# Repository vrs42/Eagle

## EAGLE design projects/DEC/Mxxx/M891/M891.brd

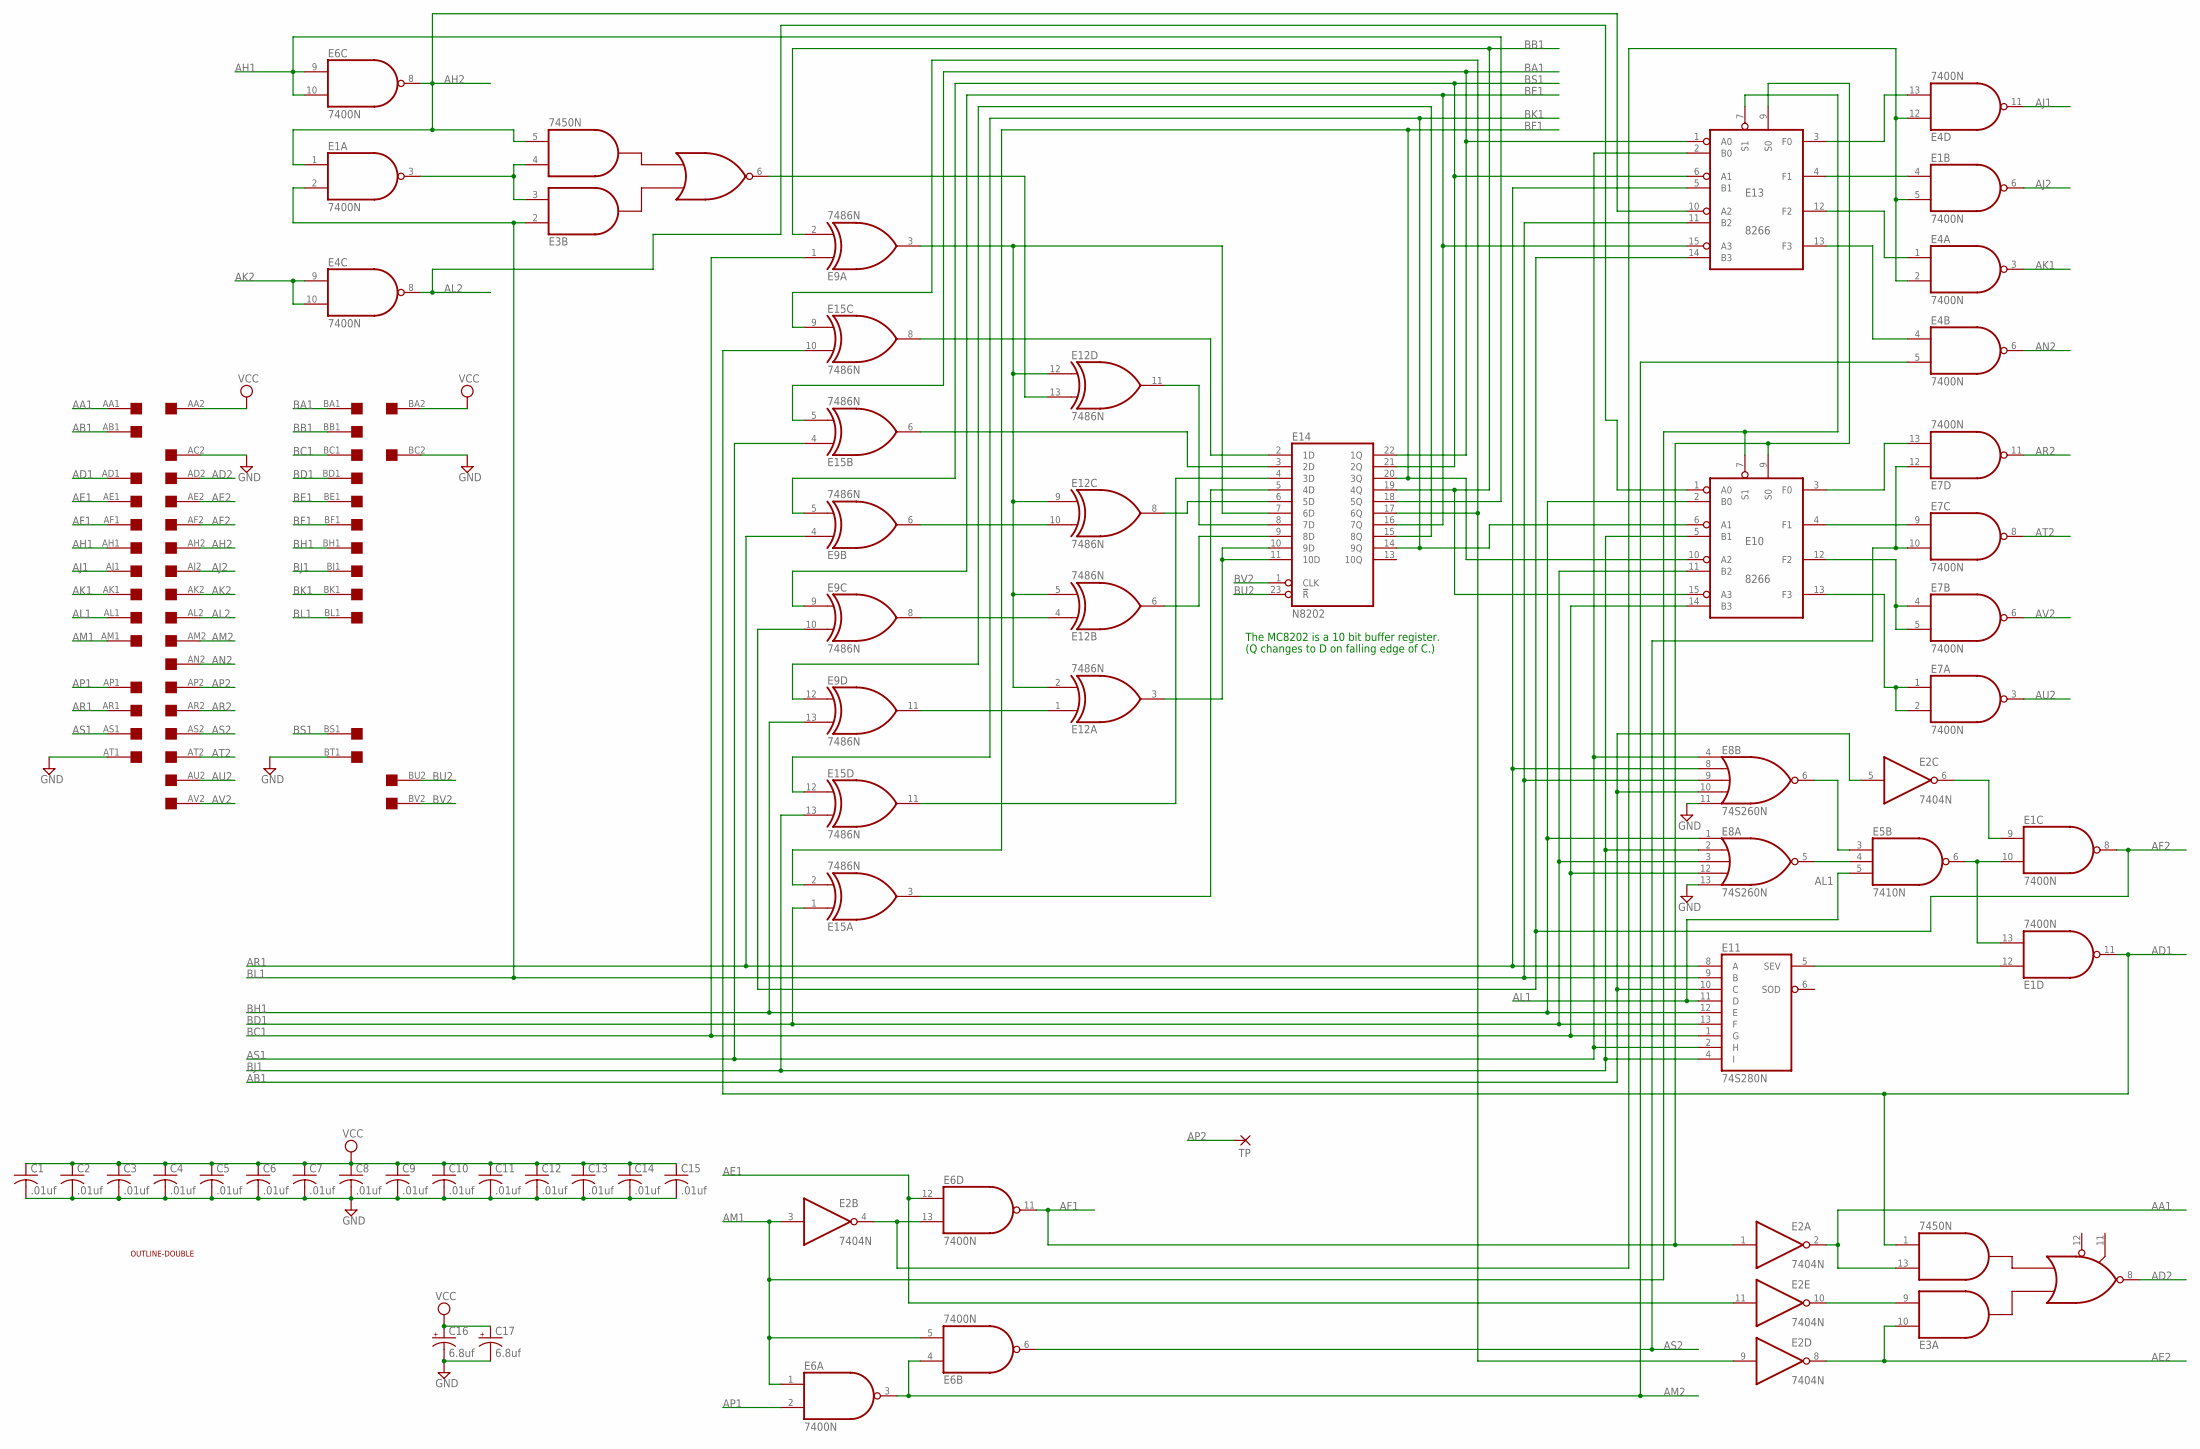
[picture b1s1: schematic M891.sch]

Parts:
C1, C2, C3, C4, C5, C6, C7, C8, C9, C10, C11, C12, C13, C14, C15: .01uf; C050-025X075
C16, C17: 6.8uf; E22-6
E1, E4, E6, E7: 7400N; DIL14
E2: 7404N; DIL14
E3: 7450N; DIL14
E5: 7410N; DIL14
E8: 74S260N; DIL14
E9, E12, E15: 7486N; DIL14
E10, E13: 8266; DIL16
E11: 74S280N; DIL14
E14: N8202; DIL24
EDGE: DOUBLE; EDGE-CON4
TP: 2,15/1,0
U$2: OUTLINE-DOUBLE; DOUBLE

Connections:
AA1: E2.2 (O), E3.13 (I3), EDGE.AA1
AB1: E2.5 (I), E8.10 (I3), E11.10 (C), EDGE.AB1
AD1: E1.11 (O), E3.1 (I4), E15.10 (I1), EDGE.AD1
AD2: E3.8 (O), EDGE.AD2
AE1: E2.11 (I), E6.12 (I0), EDGE.AE1
AE2: E2.8 (O), E3.10 (I1), EDGE.AE2
AF1: E2.1 (I), E6.11 (O), E10.9 (S0), E13.9 (S0), EDGE.AF1
AF2: E1.8 (O), E9.10 (I1), E13.14 (B3), EDGE.AF2
AH1: E6.9 (I0), E6.10 (I1), E14.18 (5Q), EDGE.AH1
AH2: E1.1 (I0), E3.5 (I4), E6.8 (O), E13.10 (A2), EDGE.AH2
AJ1: E4.11 (O), EDGE.AJ1
AJ2: E1.6 (O), EDGE.AJ2
AK1: E4.3 (O), EDGE.AK1
AK2: E4.9 (I0), E4.10 (I1), EDGE.AK2
AL1: E5.5 (I2), E11.11 (D), EDGE.AL1
AL2: E4.8 (O), E10.1 (A0), EDGE.AL2
AM1: E2.3 (I), E6.1 (I0), E6.5 (I1), E10.7 (S1), E13.7 (S1), EDGE.AM1
AM2: E4.5 (I1), E6.3 (O), E6.4 (I0), EDGE.AM2
AN2: E4.6 (O), EDGE.AN2
AP1: E6.2 (I1), EDGE.AP1
AP2: EDGE.AP2, TP.1
AR1: E8.8 (I1), E9.4 (I0), E11.8 (A), E13.5 (B1), EDGE.AR1
AR2: E7.11 (O), EDGE.AR2
AS1: E8.4 (I0), E11.2 (H), E13.2 (B0), E15.4 (I0), EDGE.AS1
AS2: E6.6 (O), E7.10 (I1), E7.12 (I0), EDGE.AS2
AT2: E7.8 (O), EDGE.AT2
AU2: E7.3 (O), EDGE.AU2
AV2: E7.6 (O), EDGE.AV2
BA1: E13.1 (A0), E14.22 (1Q), E15.5 (I1), EDGE.BA1
BB1: E9.2 (I1), E10.15 (A3), E14.19 (4Q), EDGE.BB1
BC1: E8.12 (I3), E9.1 (I0), E10.14 (B3), E11.1 (G), EDGE.BC1
BD1: E8.3 (I2), E10.11 (B2), E11.13 (F), E15.1 (I0), EDGE.BD1
BE1: E9.9 (I0), E13.15 (A3), E14.16 (7Q), EDGE.BE1
BF1: E10.10 (A2), E14.20 (3Q), E15.2 (I1), EDGE.BF1
BH1: E8.1 (I0), E9.13 (I1), E10.2 (B0), E11.12 (E), EDGE.BH1
BJ1: E8.2 (I1), E10.5 (B1), E11.4 (I), E15.13 (I1), EDGE.BJ1
BK1: E10.6 (A1), E14.14 (9Q), E15.12 (I0), EDGE.BK1
BL1: E1.2 (I1), E3.2 (I1), E8.9 (I2), E11.9 (B), E13.11 (B2), EDGE.BL1
BS1: E9.5 (I1), E13.6 (A1), E14.21 (2Q), EDGE.BS1
BU2: E14.23 (!R), EDGE.BU2
BV2: E14.1 (CLK), EDGE.BV2
GND: C1.2, C2.2, C3.2, C4.2, C5.2, C6.2, C7.2, C8.2, C9.2, C10.2, C11.2, C12.2, C13.2, C14.2, C15.2, C16.-, C17.-, E1.7 (GND), E2.7 (GND), E3.7 (GND), E4.7 (GND), E5.7 (GND), E6.7 (GND), E7.7 (GND), E8.7 (GND), E8.11 (I4), E8.13 (I4), E9.7 (GND), E10.8 (GND), E11.7 (GND), E12.7 (GND), E13.8 (GND), E14.12 (GND), E15.7 (GND), EDGE.AC2, EDGE.AT1, EDGE.BC2, EDGE.BT1
unnamed: E1.3 (O), E3.3 (I2), E3.4 (I3)
unnamed: E2.9 (I), E14.17 (6Q), E15.9 (I0)
unnamed: E1.5 (I1), E2.4 (O), E4.2 (I1), E4.12 (I0), E6.13 (I1)
unnamed: E4.13 (I1), E13.3 (F0)
unnamed: E1.4 (I0), E13.4 (F1)
unnamed: E4.1 (I0), E13.12 (F2)
unnamed: E4.4 (I0), E13.13 (F3)
unnamed: E9.12 (I0), E14.15 (8Q)
unnamed: E3.6 (O), E12.13 (I1)
unnamed: E1.12 (I0), E11.5 (SEV)
unnamed: E14.3 (2D), E15.6 (O)
unnamed: E9.3 (O), E12.2 (I1), E12.5 (I1), E12.9 (I0), E12.12 (I0), E14.7 (6D)
unnamed: E9.11 (O), E12.1 (I0)
unnamed: E9.8 (O), E12.4 (I0)
unnamed: E9.6 (O), E12.10 (I1)
unnamed: E14.2 (1D), E15.8 (O)
unnamed: E12.11 (O), E14.8 (7D)
unnamed: E14.5 (4D), E15.3 (O)
unnamed: E14.4 (3D), E15.11 (O)
unnamed: E12.8 (O), E14.6 (5D)
unnamed: E12.6 (O), E14.9 (8D)
unnamed: E12.3 (O), E14.10 (9D), E14.11 (10D)
unnamed: E7.9 (I0), E10.4 (F1)
unnamed: E7.13 (I1), E10.3 (F0)
unnamed: E7.4 (I0), E7.5 (I1), E10.12 (F2)
unnamed: E7.1 (I0), E7.2 (I1), E10.13 (F3)
unnamed: E2.10 (O), E3.9 (I2)
unnamed: E5.4 (I1), E8.5 (O)
unnamed: E5.3 (I0), E8.6 (O)
unnamed: E1.10 (I1), E1.13 (I1), E5.6 (O)
unnamed: E1.9 (I0), E2.6 (O)
VCC: C1.1, C2.1, C3.1, C4.1, C5.1, C6.1, C7.1, C8.1, C9.1, C10.1, C11.1, C12.1, C13.1, C14.1, C15.1, C16.+, C17.+, E1.14 (VCC), E2.14 (VCC), E3.14 (VCC), E4.14 (VCC), E5.14 (VCC), E6.14 (VCC), E7.14 (VCC), E8.14 (VCC), E9.14 (VCC), E10.16 (VCC), E11.14 (VCC), E12.14 (VCC), E13.16 (VCC), E14.24 (VCC), E15.14 (VCC), EDGE.AA2, EDGE.BA2

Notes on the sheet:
The MC8202 is a 10 bit buffer register.
(Q changes to D on falling edge of C.)

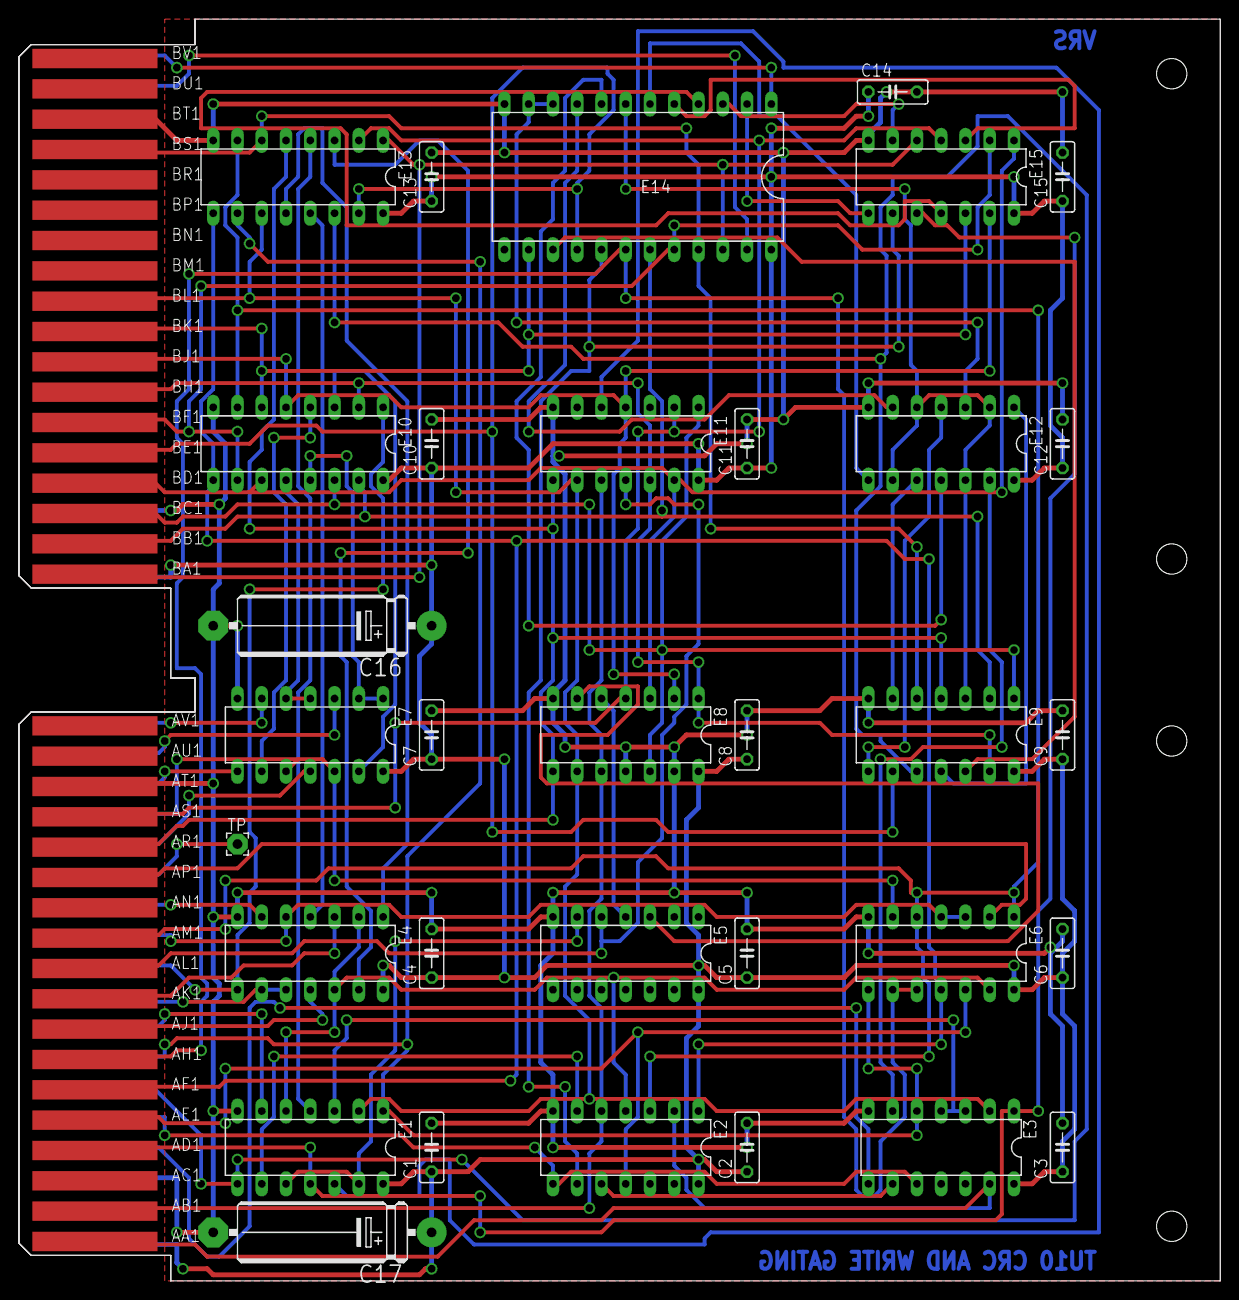
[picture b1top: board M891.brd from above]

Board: 2 copper layers, 125.7 x 132.1 mm, 35 parts (0 on the bottom side), 74 nets.

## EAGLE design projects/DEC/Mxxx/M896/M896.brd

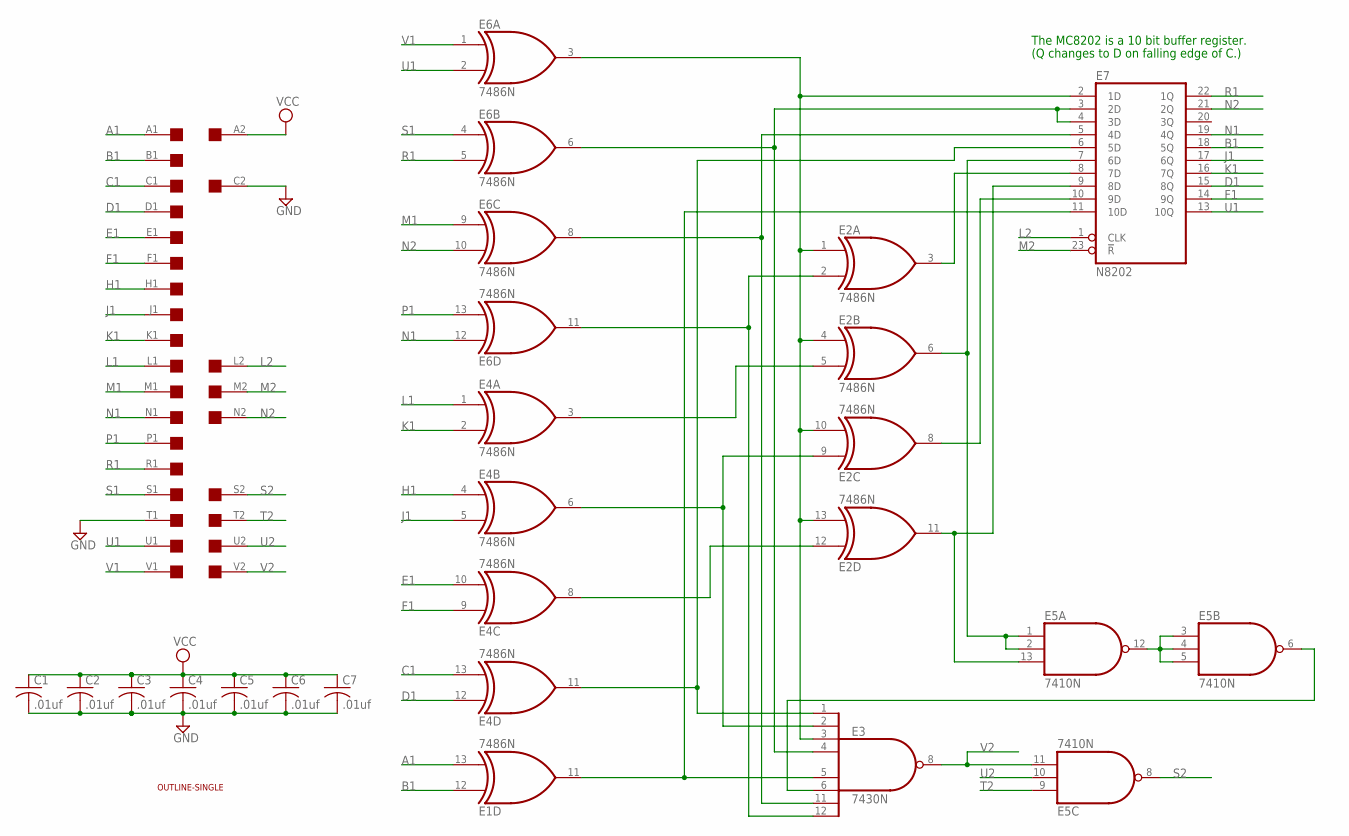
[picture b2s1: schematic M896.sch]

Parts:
C1, C2, C3, C4, C5, C6, C7: .01uf; C050-025X075
E1, E2, E4, E6: 7486N; DIL14
E3: 7430N; DIL14
E5: 7410N; DIL14
E7: N8202; DIL24
U$1: EDGE-2CONNECTOR; EDGE-CON2
U$4: OUTLINE-SINGLE; SINGLE

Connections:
A1: E1.13 (I1), U$1.A1
B1: E1.12 (I0), E7.18 (5Q), U$1.B1
C1: E4.13 (I1), U$1.C1
D1: E4.12 (I0), E7.15 (8Q), U$1.D1
E1: E4.10 (I1), U$1.E1
F1: E4.9 (I0), E7.14 (9Q), U$1.F1
GND: C1.2, C2.2, C3.2, C4.2, C5.2, C6.2, C7.2, E1.7 (GND), E2.7 (GND), E3.7 (GND), E4.7 (GND), E5.7 (GND), E6.7 (GND), E7.12 (GND), U$1.C2, U$1.T1
H1: E4.4 (I0), U$1.H1
J1: E4.5 (I1), E7.17 (6Q), U$1.J1
K1: E4.2 (I1), E7.16 (7Q), U$1.K1
L1: E4.1 (I0), U$1.L1
L2: E7.1 (CLK), U$1.L2
M1: E6.9 (I0), U$1.M1
M2: E7.23 (!R), U$1.M2
N1: E6.12 (I0), E7.19 (4Q), U$1.N1
N2: E6.10 (I1), E7.21 (2Q), U$1.N2
unnamed: E2.1 (I0), E2.4 (I0), E2.10 (I1), E2.13 (I1), E3.3 (I2), E6.3 (O), E7.2 (1D)
unnamed: E2.2 (I1), E3.12 (I7), E6.11 (O)
unnamed: E2.5 (I1), E4.3 (O)
unnamed: E2.9 (I0), E3.2 (I1), E4.6 (O)
unnamed: E2.12 (I0), E4.8 (O)
unnamed: E1.11 (O), E3.5 (I4), E7.11 (10D)
unnamed: E3.1 (I0), E4.11 (O), E7.6 (5D)
unnamed: E5.3 (I0), E5.4 (I1), E5.5 (I2), E5.12 (O)
unnamed: E3.11 (I6), E6.8 (O), E7.5 (4D)
unnamed: E3.4 (I3), E6.6 (O), E7.3 (2D), E7.4 (3D)
unnamed: E3.6 (I5), E5.6 (O)
unnamed: E2.6 (O), E5.1 (I0), E5.2 (I1), E7.7 (6D)
unnamed: E2.11 (O), E5.13 (I2), E7.9 (8D)
unnamed: E2.3 (O), E7.8 (7D)
unnamed: E2.8 (O), E7.10 (9D)
P1: E6.13 (I1), U$1.P1
R1: E6.5 (I1), E7.22 (1Q), U$1.R1
S1: E6.4 (I0), U$1.S1
S2: E5.8 (O), U$1.S2
T2: E5.9 (I0), U$1.T2
U1: E6.2 (I1), E7.13 (10Q), U$1.U1
U2: E5.10 (I1), U$1.U2
V1: E6.1 (I0), U$1.V1
V2: E3.8 (O), E5.11 (I2), U$1.V2
VCC: C1.1, C2.1, C3.1, C4.1, C5.1, C6.1, C7.1, E1.14 (VCC), E2.14 (VCC), E3.14 (VCC), E4.14 (VCC), E5.14 (VCC), E6.14 (VCC), E7.24 (VCC), U$1.A2

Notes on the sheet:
The MC8202 is a 10 bit buffer register.
(Q changes to D on falling edge of C.)

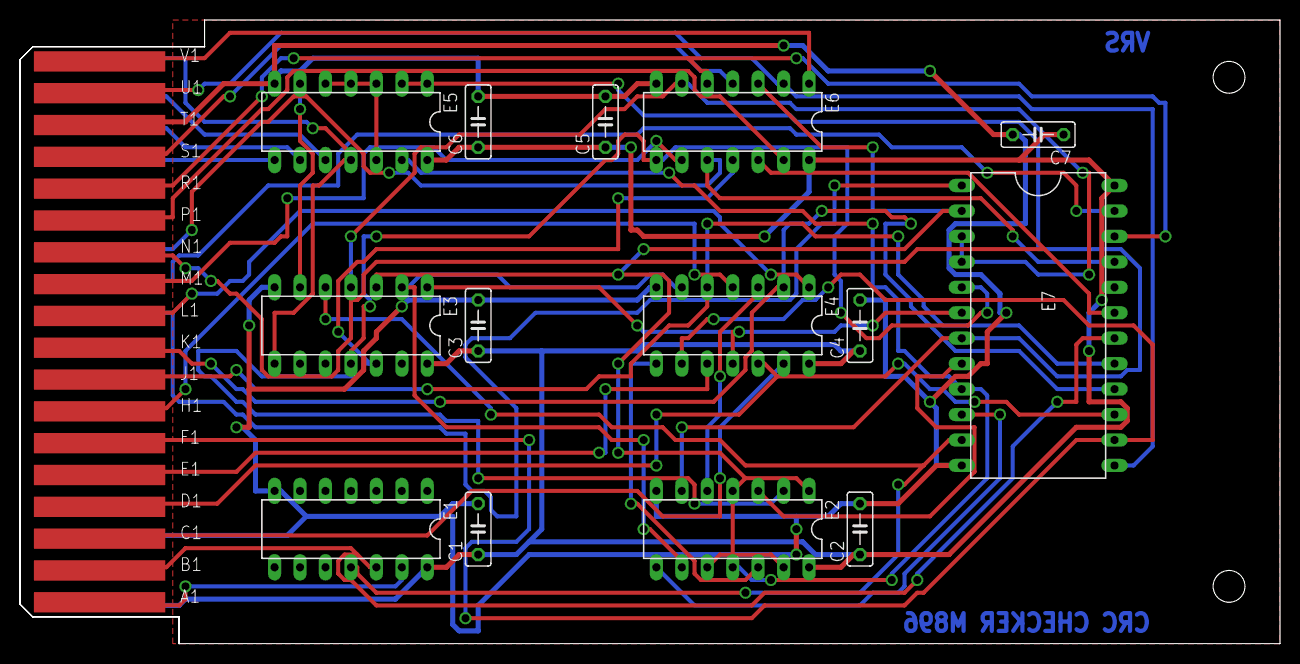
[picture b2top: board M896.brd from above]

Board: 2 copper layers, 125.7 x 62.2 mm, 16 parts (0 on the bottom side), 41 nets.

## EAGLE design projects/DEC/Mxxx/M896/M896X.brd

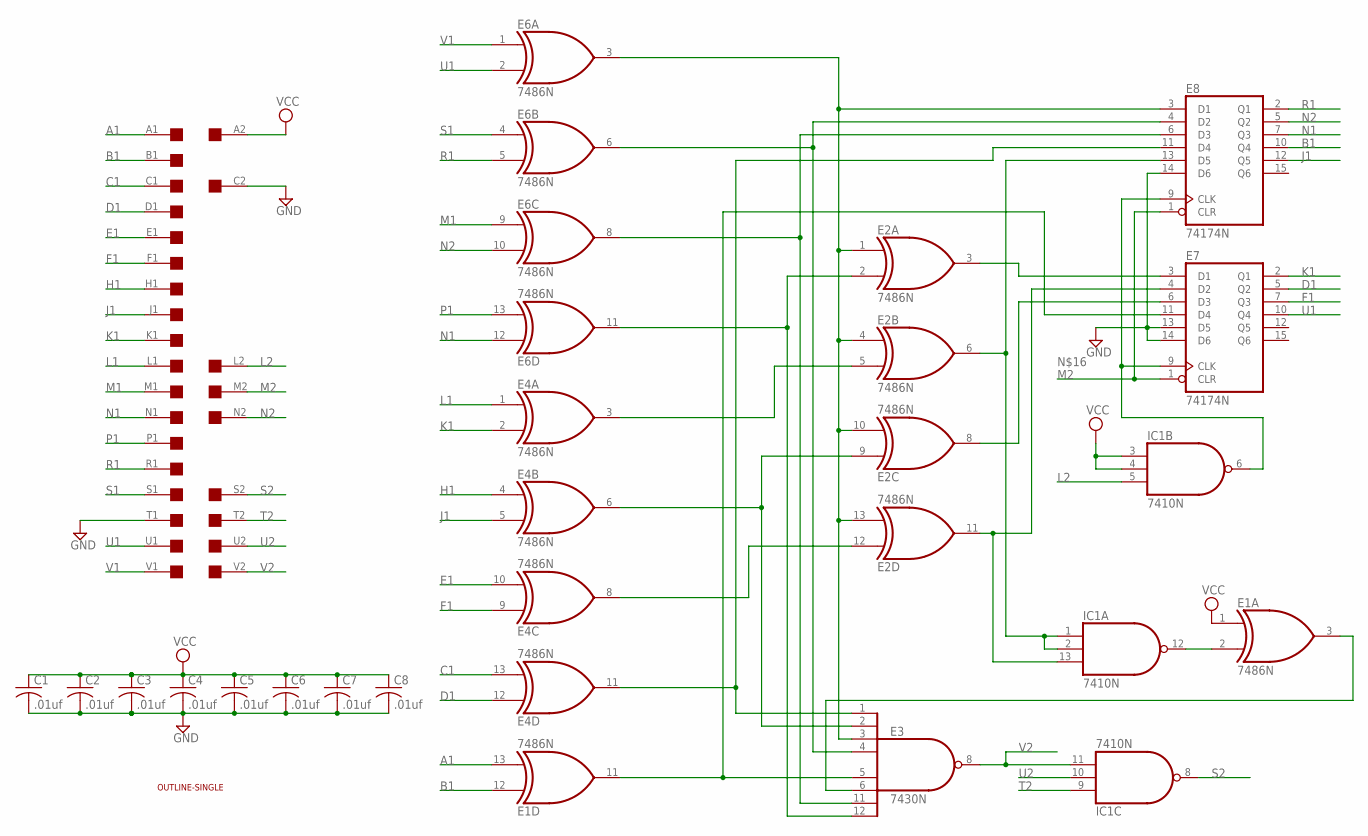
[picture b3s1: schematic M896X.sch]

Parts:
C1, C2, C3, C4, C5, C6, C7, C8: .01uf; C050-025X075
E1, E2, E4, E6: 7486N; DIL14
E3: 7430N; DIL14
E7, E8: 74174N; DIL16
IC1: 7410N; DIL14
U$1: EDGE-2CONNECTOR; EDGE-CON2
U$4: OUTLINE-SINGLE; SINGLE

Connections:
A1: E1.13 (I1), U$1.A1
B1: E1.12 (I0), E8.10 (Q4), U$1.B1
C1: E4.13 (I1), U$1.C1
D1: E4.12 (I0), E7.5 (Q2), U$1.D1
E1: E4.10 (I1), U$1.E1
F1: E4.9 (I0), E7.7 (Q3), U$1.F1
GND: C1.2, C2.2, C3.2, C4.2, C5.2, C6.2, C7.2, C8.2, E1.7 (GND), E2.7 (GND), E3.7 (GND), E4.7 (GND), E6.7 (GND), E7.8 (GND), E7.13 (D5), E7.14 (D6), E8.8 (GND), E8.14 (D6), IC1.7 (GND), U$1.C2, U$1.T1
H1: E4.4 (I0), U$1.H1
J1: E4.5 (I1), E8.12 (Q5), U$1.J1
K1: E4.2 (I1), E7.2 (Q1), U$1.K1
L1: E4.1 (I0), U$1.L1
L2: IC1.5 (I2), U$1.L2
M1: E6.9 (I0), U$1.M1
M2: E7.1 (CLR), E8.1 (CLR), U$1.M2
N1: E6.12 (I0), E8.7 (Q3), U$1.N1
N2: E6.10 (I1), E8.5 (Q2), U$1.N2
unnamed: E2.1 (I0), E2.4 (I0), E2.10 (I1), E2.13 (I1), E3.3 (I2), E6.3 (O), E8.3 (D1)
unnamed: E2.2 (I1), E3.12 (I7), E6.11 (O)
unnamed: E2.5 (I1), E4.3 (O)
unnamed: E2.9 (I0), E3.2 (I1), E4.6 (O)
unnamed: E2.12 (I0), E4.8 (O)
unnamed: E1.11 (O), E3.5 (I4), E7.11 (D4)
unnamed: E3.1 (I0), E4.11 (O), E8.11 (D4)
unnamed: E1.2 (I1), IC1.12 (O)
unnamed: E3.11 (I6), E6.8 (O), E8.6 (D3)
unnamed: E3.4 (I3), E6.6 (O), E8.4 (D2)
unnamed: E1.3 (O), E3.6 (I5)
unnamed: E2.6 (O), E8.13 (D5), IC1.1 (I0), IC1.2 (I1)
unnamed: E2.11 (O), E7.4 (D2), IC1.13 (I2)
unnamed: E2.3 (O), E7.3 (D1)
unnamed: E2.8 (O), E7.6 (D3)
unnamed: E7.9 (CLK), E8.9 (CLK), IC1.6 (O)
P1: E6.13 (I1), U$1.P1
R1: E6.5 (I1), E8.2 (Q1), U$1.R1
S1: E6.4 (I0), U$1.S1
S2: IC1.8 (O), U$1.S2
T2: IC1.9 (I0), U$1.T2
U1: E6.2 (I1), E7.10 (Q4), U$1.U1
U2: IC1.10 (I1), U$1.U2
V1: E6.1 (I0), U$1.V1
V2: E3.8 (O), IC1.11 (I2), U$1.V2
VCC: C1.1, C2.1, C3.1, C4.1, C5.1, C6.1, C7.1, C8.1, E1.1 (I0), E1.14 (VCC), E2.14 (VCC), E3.14 (VCC), E4.14 (VCC), E6.14 (VCC), E7.16 (VCC), E8.16 (VCC), IC1.3 (I0), IC1.4 (I1), IC1.14 (VCC), U$1.A2

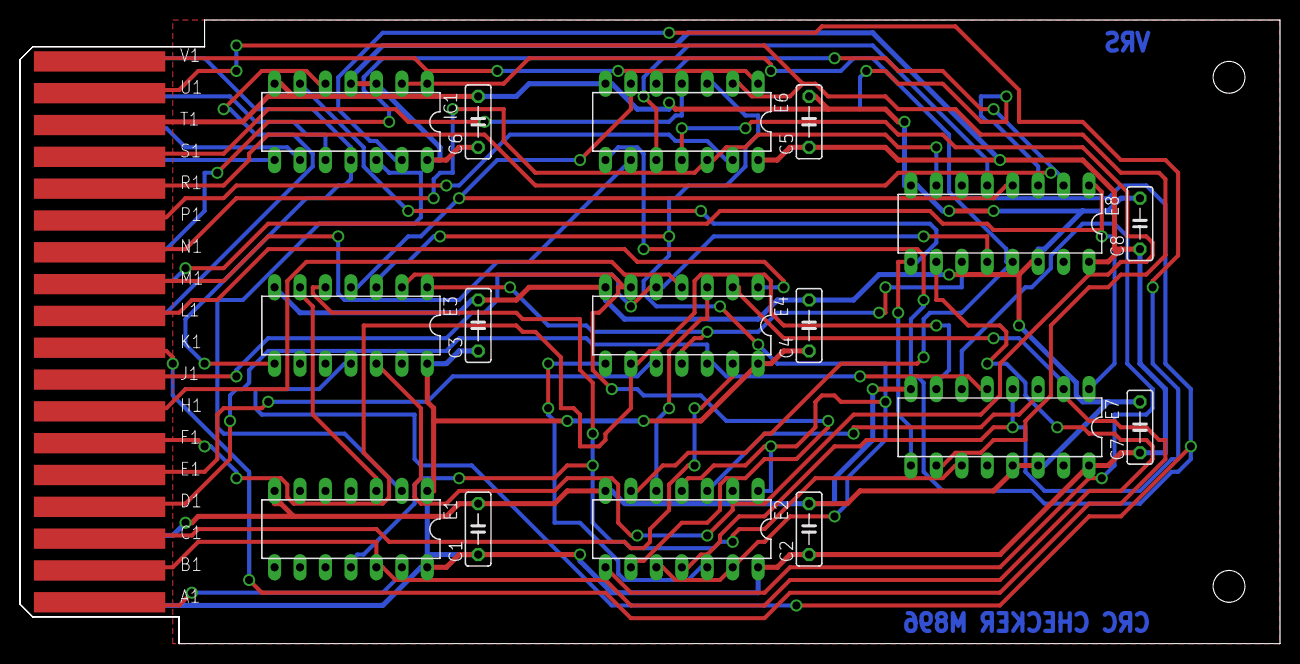
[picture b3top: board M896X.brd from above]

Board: 2 copper layers, 125.7 x 62.2 mm, 18 parts (0 on the bottom side), 42 nets.

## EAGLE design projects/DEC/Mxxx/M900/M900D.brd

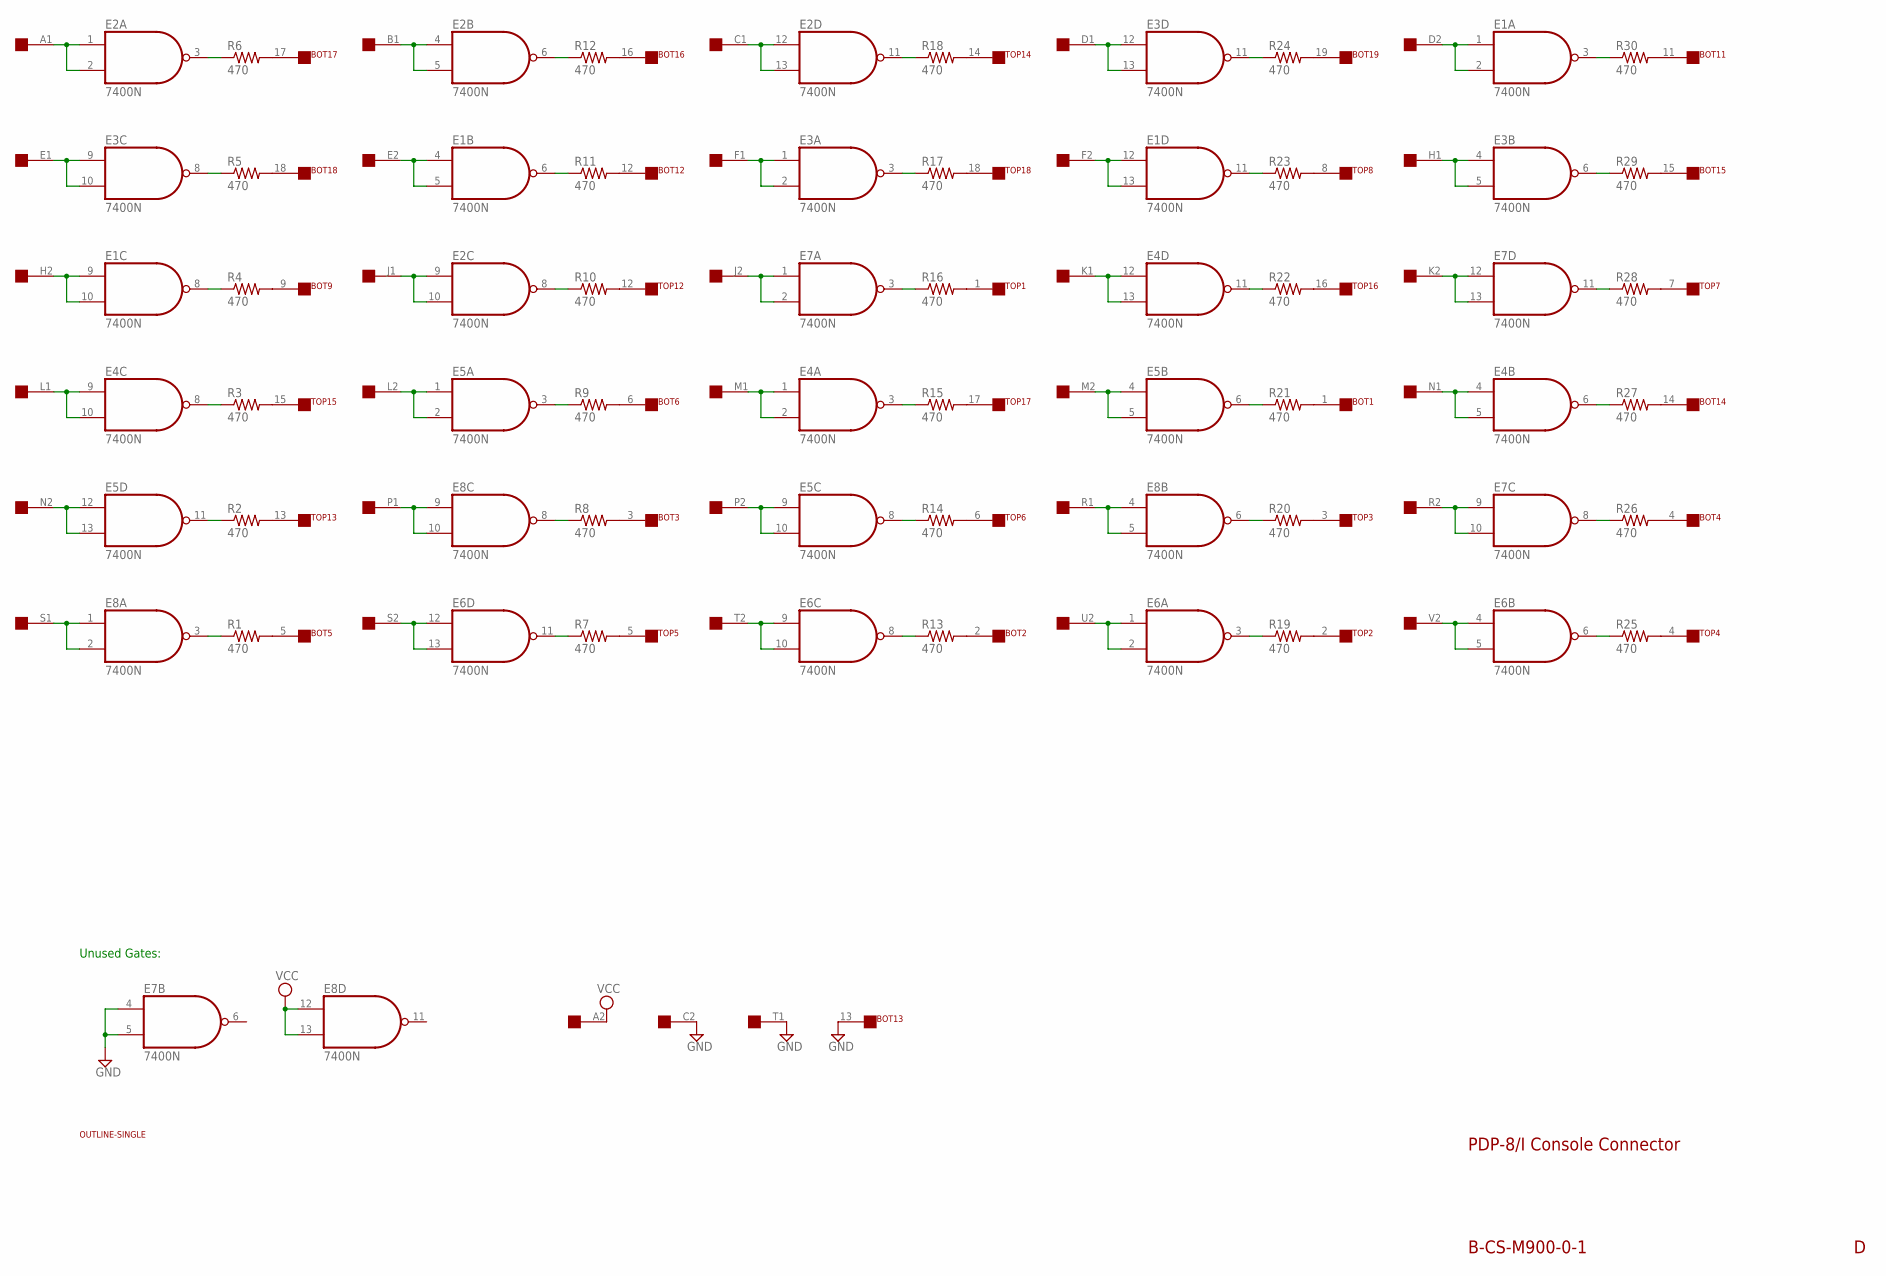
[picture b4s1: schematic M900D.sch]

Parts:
BOT: FLEX19
E1, E2, E3, E4, E5, E6, E7, E8: 7400N; DIL14
EDGE: SINGLE; EDGE-CON2
R1, R2, R3, R4, R5, R6, R7, R8, R9, R10, R11, R12, R13, R14, R15, R16, R17, R18, R19, R20, R21, R22, R23, R24, R25, R26, R27, R28, R29, R30: 470; 0207/10
TOP: FLEX19
U$2: OUTLINE-SINGLE; SINGLE

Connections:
GND: BOT.13, E1.7 (GND), E2.7 (GND), E3.7 (GND), E4.7 (GND), E5.7 (GND), E6.7 (GND), E7.4 (I0), E7.5 (I1), E7.7 (GND), E8.7 (GND), EDGE.C2, EDGE.T1
unnamed: E2.1 (I0), E2.2 (I1), EDGE.A1
unnamed: E2.3 (O), R6.1
unnamed: E3.8 (O), R5.1
unnamed: E1.8 (O), R4.1
unnamed: E4.8 (O), R3.1
unnamed: E5.11 (O), R2.1
unnamed: E1.9 (I0), E1.10 (I1), EDGE.H2
unnamed: E8.1 (I0), E8.2 (I1), EDGE.S1
unnamed: E5.12 (I0), E5.13 (I1), EDGE.N2
unnamed: E4.9 (I0), E4.10 (I1), EDGE.L1
unnamed: E3.9 (I0), E3.10 (I1), EDGE.E1
unnamed: E8.9 (I0), E8.10 (I1), EDGE.P1
unnamed: E2.4 (I0), E2.5 (I1), EDGE.B1
unnamed: E1.4 (I0), E1.5 (I1), EDGE.E2
unnamed: E2.9 (I0), E2.10 (I1), EDGE.J1
unnamed: E5.1 (I0), E5.2 (I1), EDGE.L2
unnamed: E6.12 (I0), E6.13 (I1), EDGE.S2
unnamed: E8.8 (O), R8.1
unnamed: E5.3 (O), R9.1
unnamed: E2.8 (O), R10.1
unnamed: E1.6 (O), R11.1
unnamed: E2.6 (O), R12.1
unnamed: E6.11 (O), R7.1
unnamed: E8.3 (O), R1.1
unnamed: E5.9 (I0), E5.10 (I1), EDGE.P2
unnamed: E2.12 (I0), E2.13 (I1), EDGE.C1
unnamed: E3.1 (I0), E3.2 (I1), EDGE.F1
unnamed: E7.1 (I0), E7.2 (I1), EDGE.J2
unnamed: E4.1 (I0), E4.2 (I1), EDGE.M1
unnamed: E6.9 (I0), E6.10 (I1), EDGE.T2
unnamed: E6.8 (O), R13.1
unnamed: E5.8 (O), R14.1
unnamed: E4.3 (O), R15.1
unnamed: E7.3 (O), R16.1
unnamed: E2.11 (O), R18.1
unnamed: E3.3 (O), R17.1
unnamed: E6.3 (O), R19.1
unnamed: E8.6 (O), R20.1
unnamed: E5.6 (O), R21.1
unnamed: E4.11 (O), R22.1
unnamed: E1.11 (O), R23.1
unnamed: E3.11 (O), R24.1
unnamed: E8.4 (I0), E8.5 (I1), EDGE.R1
unnamed: E1.12 (I0), E1.13 (I1), EDGE.F2
unnamed: E4.12 (I0), E4.13 (I1), EDGE.K1
unnamed: E5.4 (I0), E5.5 (I1), EDGE.M2
unnamed: E6.1 (I0), E6.2 (I1), EDGE.U2
unnamed: E7.9 (I0), E7.10 (I1), EDGE.R2
unnamed: E3.12 (I0), E3.13 (I1), EDGE.D1
unnamed: E1.1 (I0), E1.2 (I1), EDGE.D2
unnamed: E3.4 (I0), E3.5 (I1), EDGE.H1
unnamed: E7.12 (I0), E7.13 (I1), EDGE.K2
unnamed: E4.4 (I0), E4.5 (I1), EDGE.N1
unnamed: E6.4 (I0), E6.5 (I1), EDGE.V2
unnamed: E6.6 (O), R25.1
unnamed: E7.8 (O), R26.1
unnamed: E4.6 (O), R27.1
unnamed: E7.11 (O), R28.1
unnamed: E3.6 (O), R29.1
unnamed: E1.3 (O), R30.1
unnamed: R17.2, TOP.18
unnamed: R15.2, TOP.17
unnamed: R22.2, TOP.16
unnamed: R3.2, TOP.15
unnamed: R18.2, TOP.14
unnamed: R2.2, TOP.13
unnamed: R10.2, TOP.12
unnamed: R23.2, TOP.8
unnamed: R28.2, TOP.7
unnamed: R14.2, TOP.6
unnamed: R7.2, TOP.5
unnamed: R25.2, TOP.4
unnamed: R20.2, TOP.3
unnamed: R19.2, TOP.2
unnamed: R16.2, TOP.1
unnamed: BOT.15, R29.2
unnamed: BOT.3, R8.2
unnamed: BOT.1, R21.2
unnamed: BOT.2, R13.2
unnamed: BOT.4, R26.2
unnamed: BOT.5, R1.2
unnamed: BOT.19, R24.2
unnamed: BOT.18, R5.2
unnamed: BOT.17, R6.2
unnamed: BOT.16, R12.2
unnamed: BOT.14, R27.2
unnamed: BOT.12, R11.2
unnamed: BOT.9, R4.2
unnamed: BOT.6, R9.2
unnamed: BOT.11, R30.2
VCC: E1.14 (VCC), E2.14 (VCC), E3.14 (VCC), E4.14 (VCC), E5.14 (VCC), E6.14 (VCC), E7.14 (VCC), E8.12 (I0), E8.13 (I1), E8.14 (VCC), EDGE.A2

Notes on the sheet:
Unused Gates:
B-CS-M900-0-1
PDP-8/I Console Connector

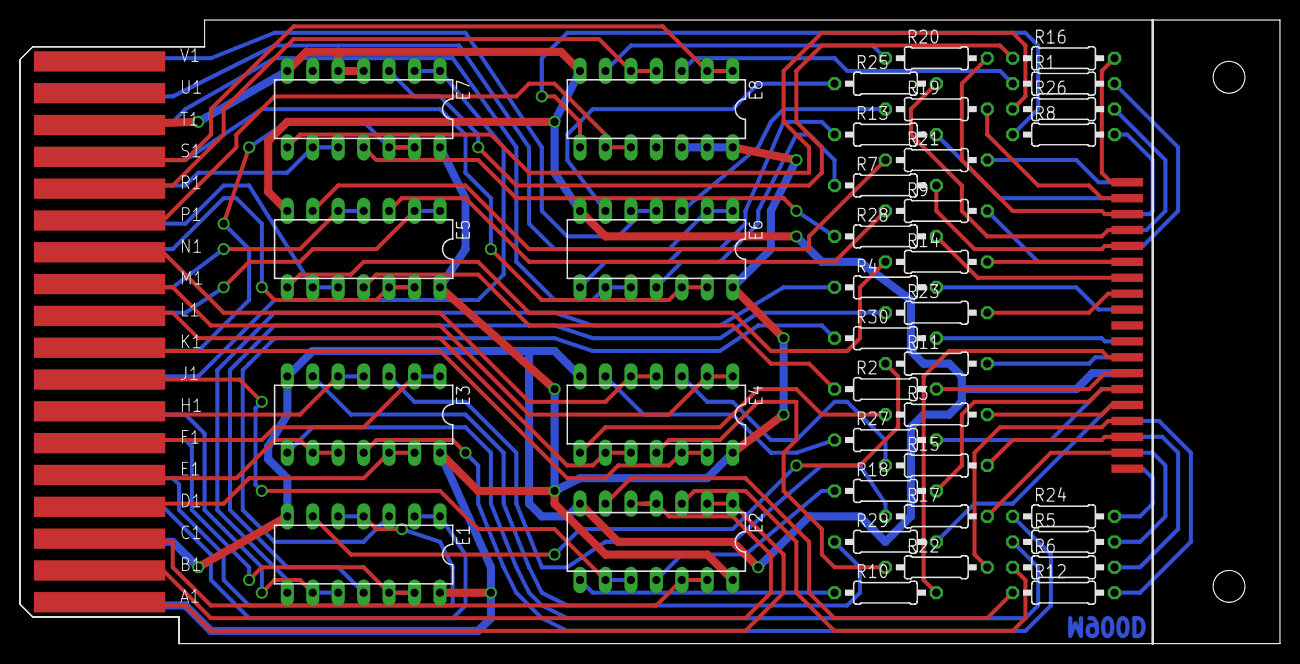
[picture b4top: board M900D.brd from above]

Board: 2 copper layers, 125.7 x 62.2 mm, 42 parts (1 on the bottom side), 92 nets.
